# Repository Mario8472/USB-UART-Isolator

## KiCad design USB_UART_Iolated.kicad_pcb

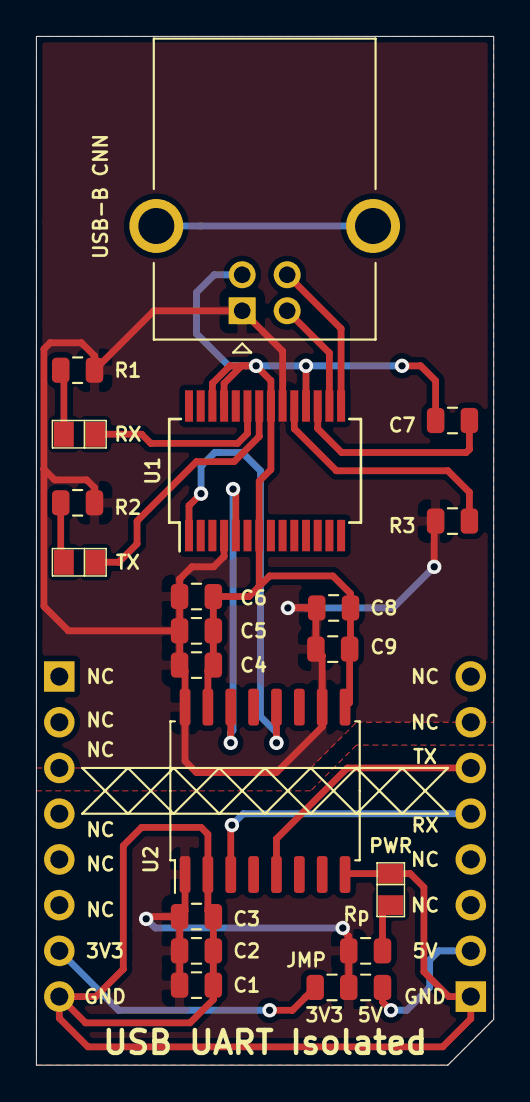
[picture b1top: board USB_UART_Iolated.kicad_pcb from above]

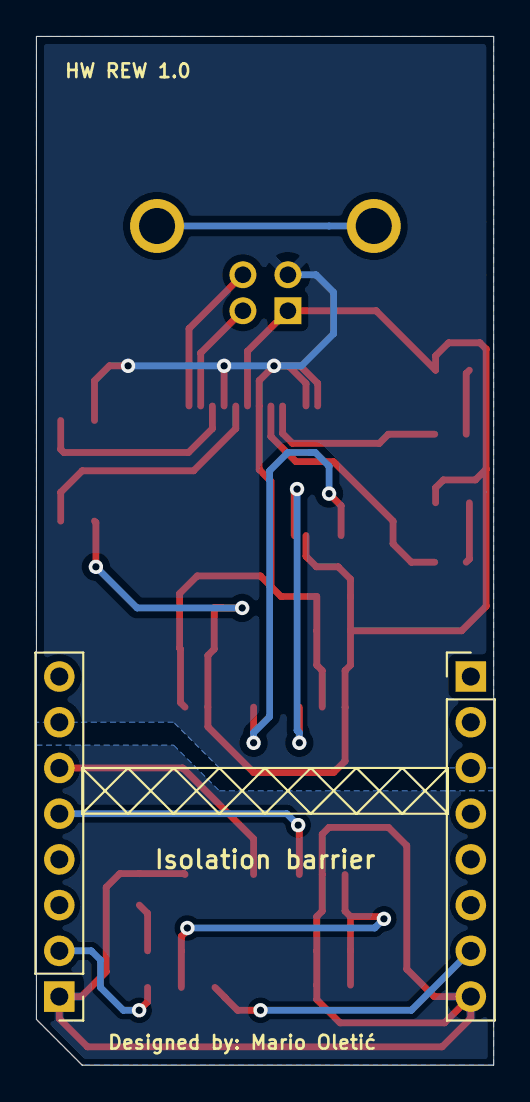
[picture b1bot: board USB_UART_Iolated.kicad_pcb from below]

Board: 2 copper layers, 25.4 x 57.2 mm, 22 parts (2 on the bottom side), 19 nets.

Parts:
C1, C2, C3, C4, C5, C6: C; C_0805_2012Metric
C7, C8, C9: 100nF; C_0805_2012Metric
CN1, CN2: HeaderPin_1x8_2.54mm; PinHeader_1x08_P2.54mm_Vertical
JMP: JUMPER_0805; Jumper_0805
PWR: LED0805
R1, R2: 2k2; R_0805_2012Metric
R3: R; R_0805_2012Metric
RX: LED0805
Rp: 4k7; R_0805_2012Metric
TX: LED0805
U1: FT232RL; SSOP-28_5.3x10.2mm_P0.65mm
U2: ISOW7842; ISOW784x
USB-B CNN: USB-B_CONN

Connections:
/3V3: CN1.7, JMP.3
/5V: CN2.2, JMP.1
/D+: U1.15, USB-B CNN.3
/D-: U1.16, USB-B CNN.2
/RX: U1.5, U2.14
/TX: U1.1, U2.12
/mB_RX: CN2.5, U2.3
/mB_TX: CN2.6, U2.5
GND: C4.2, C5.2, C6.2, C7.1, C8.2, C9.2, U1.7, U1.18, U1.21, U1.25, U1.26, U2.9, U2.15, USB-B CNN.4
GNDA: C1.2, C2.2, C3.2, CN1.8, CN2.1, PWR.2, U2.2, U2.8
unnamed: C7.2, U1.17
unnamed: PWR.1, Rp.2
unnamed: R1.2, RX.1
unnamed: R2.2, TX.1
unnamed: R3.2, U1.19
unnamed: RX.2, U1.23
unnamed: TX.2, U1.22
VCC: C4.1, C5.1, C6.1, C8.1, C9.1, R1.1, R2.1, R3.1, U1.4, U1.20, U2.10, U2.16, USB-B CNN.1
VCCQ: C1.1, C2.1, C3.1, JMP.2, Rp.1, U2.1
